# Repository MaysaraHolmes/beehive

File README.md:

# Real-Time Beehive Monitoring

We want to help beekeepers to keep an eye on their bees. By giving them insight on critical measurements we can monitor different events such as too low temperature, too high moisture, sufficient weight to harvest honey, as well as giving an estimate of how many bees went out of the beehive harvesting.

This project aims to set up a weather station with sensors and a fan to control the atmosphere inside the hive. The sensors output can be visualized through a website that can be hosted either locally on the Raspberry Pi, or hosted on the cloud (example [here](https://beehiveproject.herokuapp.com/)).
This project is done in partnership with the [Glasgow University Beekeeping Society](https://www.facebook.com/GUBeekeepingSociety/)

It was a success ! The Pi was able to make measurement of the ambiant temperature, pressure and humidity, as well as start the fan when the humidity got too high.

The website was displaying the value every 2 seconds while the fan was starting in as soon as the sensors triggered the alarm through a processor interrupt. Note, however, that the sensor provide data at more than 50Hz but it was decided the cap it to 2 second to avoid high traffic on the server (if hosted on the cloud).

## Table of contents
* [Setup](#setup)
* [General info](#general-info)
* [Technologies](#technologies)
* [Authors](#authors)
* [Images](#images)
* [Social media](#social-media)
## Setup

Instructions for installation can be found on the [installation wiki](https://github.com/MaysaraHolmes/beehive/wiki/Installation).

## General info
The code is simplified divided into three. Client, server and Fan. <br />
* The client is inteerupt by a timer every x millisecond reading the sensor data and sending it via udp to the server. <br />
* The server publish the data to our [example webpage](https://beehiveproject.herokuapp.com/) and saves the data to a database.
Additionally the server will send an email to registrered email-addresses everytime the humidity inside the beehive is too high. <br />
The website can be hosted either on a locally run server on the Raspberry Pi or hosted on a cloud based server.<br />
* The Fan is run depending on only one input pin. This pin is connected to the alarm on the humidity sensor inside the fan and will toggle instantaneously if the humidity goes above 80% humidity and off if it goes under 75% humidity. If the alarm pin toggles, it triggers an thread which will start or stop the fan depending if the pin goes high or low respectively. <br />
By this architecture the fan will be triggered even if the main code or the i2c bus fails to read the sensors. Making the code responsive and reliable. On the other hand if the alarm pin is disconnected you will still get an email/display on the webpage that the humidity inside the beehive is too high.
<br />
<br />
This projects architecture diagram:

Dependency graph for the C++ code:

The doxygen generated c++ documentation can be found here: [beehive_code_documentation](https://github.com/MaysaraHolmes/beehive/blob/master/documentation/beehive_code_documentation.pdf)

## Technologies

Project is created with:
* Raspberry pi 3.0
* Sensors
	* ADC101C021 ADC
	* HIH6131 Temperatur & Humidity x2
	* MPL115A2 Barometer
	* P82B96 I2C Shifter
* Node Js/express Js server
* MySQL database.
* [WiringPi](http://wiringpi.com/reference/core-functions/) 
* [CppTimer.h](https://github.com/berndporr/cppTimer) 

## Authors

* **Remy Chatel, 2411062**  - [Github](https://github.com/RemyChatel) (Main responsibility: Hardware)

* **Maysara Alhindi, 2417665**  - [Github](https://github.com/MaysaraHolmes) (Main responsibility: Nodejs Server side and Front-end)

* **Trine Ødegård Olsen, 2420036**  - [Github](https://github.com/trineoo) (Main responsibility: C++ code)

## Images

The beehives in the backyard in the university of Glasgow

Picture of the hardware, without the fan, soldered

## Social media
* [Hackster](https://www.hackster.io/maysara-alhindi/real-time-beehive-monitoring-glasgow-university-5a986c?fbclid=IwAR0-vXvfKS6yhzB5cdmx6wDfkbD9QhEtdo_F_e8NovsFujnpzO1nPfwy76o)
* [Hackaday](https://hackaday.io/project/164984-real-time-beehive-monitoring-glasgow-university)
* [Glasgow University Beekeeping Society](https://www.facebook.com/GUBeekeepingSociety/)

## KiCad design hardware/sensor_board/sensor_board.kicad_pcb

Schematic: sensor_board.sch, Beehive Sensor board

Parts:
C1: 0.1µ; C_0805_2012Metric_Pad1.15x1.40mm_HandSolder
C2: 0.22µ; C_0805_2012Metric_Pad1.15x1.40mm_HandSolder
C3, C4: 1µ; C_1206_3216Metric_Pad1.42x1.75mm_HandSolder
C5: 100n; C_0805_2012Metric_Pad1.15x1.40mm_HandSolder
J1: Conn_01x04; Molex_KK-254_AE-6410-04A_1x04_P2.54mm_Vertical
R1, R2, R3, R4, R5, R6: R; R_0805_2012Metric_Pad1.15x1.40mm_HandSolder
U1: HIHxx3x-021; SOIC-8_3.9x4.9mm_P1.27mm
U2: P82B96; SOIC-8_3.9x4.9mm_P1.27mm
U3: MPL115A2; LGA-8_3x5mm_P1.25mm

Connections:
+3V3: C2.1, C4.1, C5.1, J1.1, R1.1, R2.1, R3.1, R4.1, R5.2, R6.2, U1.8 (VDD), U2.8 (VCC), U3.1 (VDD)
/SCL: R2.2, U1.3 (SCL), U2.7 (SCL), U3.8 (SCL)
/SCL_ext: J1.2, R4.2, U2.2 (RXD-SDA), U2.3 (TXD-SDA)
/SDA: R1.2, U1.4 (SDA), U2.1 (SDA), U3.7 (SDA)
/SDA_ext: J1.3, R3.2, U2.5 (TXD-SCL), U2.6 (RXD-SCL)
/Vcore: C1.1, U1.1 (Vcore)
/alarm: U1.5 (AL_H)
GND: C1.2, C2.2, C3.2, C4.2, C5.2, J1.4, U1.2 (VSS), U2.4 (GND), U3.3 (GND)
unnamed: C3.1, U3.2 (CAP)
unnamed: R5.1, U3.5 (~RST)
unnamed: R6.1, U3.4 (~SHDN)

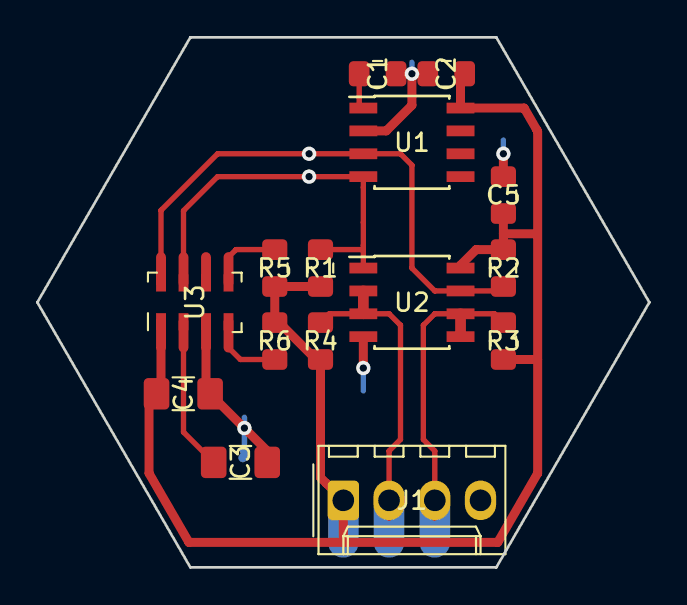
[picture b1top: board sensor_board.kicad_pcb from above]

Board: 2 copper layers, 34.0 x 29.4 mm, 15 parts (0 on the bottom side), 10 nets.

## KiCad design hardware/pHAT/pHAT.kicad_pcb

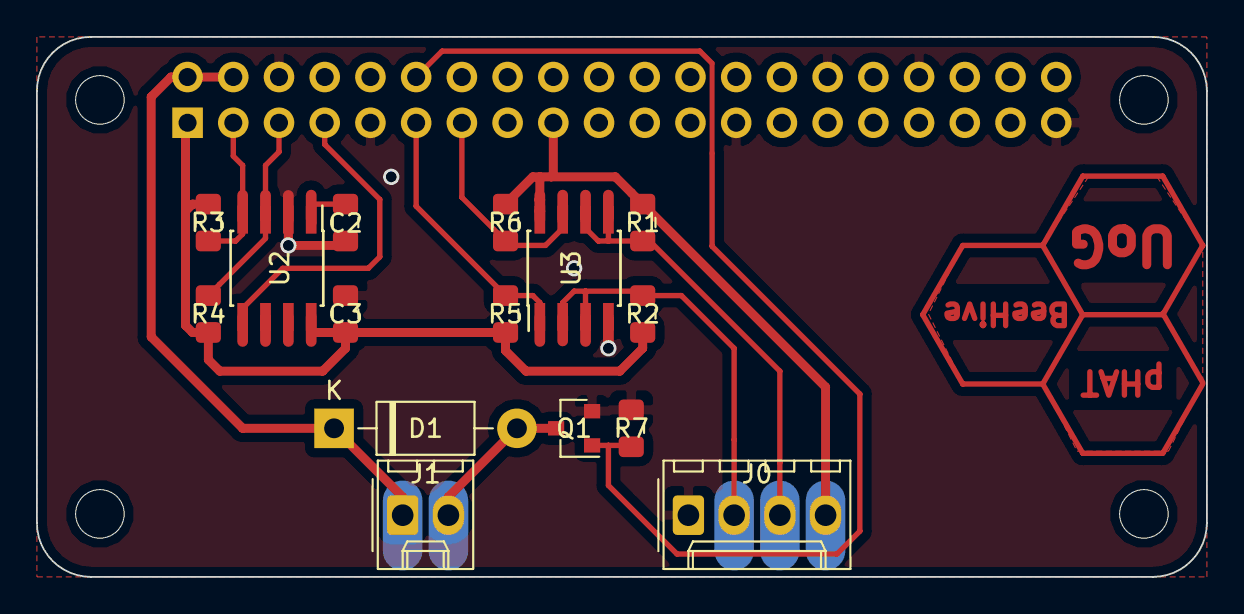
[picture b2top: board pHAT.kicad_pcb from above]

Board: 2 copper layers, 65.0 x 30.0 mm, 20 parts (1 on the bottom side), 13 nets.

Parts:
C2: 0.1µ; C_0805_2012Metric_Pad1.15x1.40mm_HandSolder
C3: 0.22µ; C_0805_2012Metric_Pad1.15x1.40mm_HandSolder
D1: 1N4007; D_DO-41_SOD81_P10.16mm_Horizontal
J0: Conn_01x04; Molex_KK-254_AE-6410-04A_1x04_P2.54mm_Vertical
J1: Conn_01x02; Molex_KK-254_AE-6410-02A_1x02_P2.54mm_Vertical
MK1, MK2, MK3, MK4: M2.5; MountingHole_2.7mm_M2.5
P1: Conn_02x20_Odd_Even; PinSocket_2x20_P2.54mm_Vertical
Q1: 2N7002; SOT-23
R1, R2, R3, R4, R5, R6, R7: 5K; R_0805_2012Metric_Pad1.15x1.40mm_HandSolder
U2: HIH6131-021; SOIC-8_3.9x4.9mm_P1.27mm
U3: P82B96; SOIC-8_3.9x4.9mm_P1.27mm

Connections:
+3V3: C3.1, J0.4, P1.1, P1.17, R1.1, R2.1, R3.1, R4.1, R5.1, R6.1, U2.8, U3.8
+5V: D1.1, J1.1, P1.2, P1.4
/SCL0: P1.5, R4.2, U2.3
/SCL1: P1.13, R6.2, U3.7
/SCLA: J0.3, R1.2, U3.5, U3.6
/SDA0: P1.3, R3.2, U2.4
/SDA1: P1.11, R5.2, U3.1
/SDAA: J0.2, R2.2, U3.2, U3.3
/Vcore: C2.1, U2.1
/alarm_hive: P1.7, U2.5
/cmd: P1.12, Q1.1, R7.1
/fan_cmd: D1.2, J1.2, Q1.3
GND: C2.2, C3.2, J0.1, P1.6, P1.9, P1.14, P1.20, P1.25, P1.30, P1.34, P1.39, Q1.2, R7.2, U2.2, U3.4

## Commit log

2019-01-18 init server
2019-01-18 datasheet upload
    Uploading datasheets of the various components (ADC, I2C multiplexer, and sensors)
2019-01-20 basic front-end desing
2019-01-21 pHAT base board
    Creation of the pHAT board
2019-01-21 First version of PCB for pHAT
2019-01-22 graphical improvements to PCB
    Added a logo and cleaned some tracks
2019-01-22 First version of sensor board
    Added a sensor board for the HIH61 humidity and temperature sensor
2019-01-22 add system folder with some basic files to test
2019-01-23 small changes to test on the raspberry
2019-01-23 Testing I2C on RPI
2019-01-23 add charts
2019-01-23 Adding documentation
2019-01-23 Moving form multiplexer to two I2C busses
    Changed from using one I2C bus with a multiplexer to using two I2C busses with the addition of level shifters
2019-01-26 Sensor board v2 and improvements to pHAT
    Added a I2C level shifter to the sensor board, which lead to a complete redesign
    Some graphical improvements to the pHAT
2019-01-28 adding pic
2019-01-28 Added ArchitectureDiagram.xml for presentation
2019-01-28 Added architecture diagram image
2019-01-28 Updated Architecture Diagram
2019-01-29 Added the alarm pin for humidity
    Added support for the alarm pin of the HIH6131 in order to detect through interrupt a high level of humidity
2019-01-30 add makefile
2019-01-30 Adding smd pad for connectors
    Adding SMD pads to allow surface soldering at right angle of Molex JYK connectors
2019-01-30 add makefile to src/system
2019-01-30 changed the makefile, use make run
2019-01-30 added smalle changes to read the i2c buffer
2019-01-30 testing bitset
2019-01-30 bitset workinggit status
2019-01-31 add the temp and hum module, but need to check MSB and LSB
2019-01-31 add the humidity equation
2019-02-02 add small changes to the I2C and TemperaturAndHumidity
2019-02-02 change the I2C template, add template ADC
2019-02-06 testing temp&hum
2019-02-06 print sentence
2019-02-06 make global_buffer
2019-02-06 add print sentence
2019-02-06 add print
2019-02-06 print
2019-02-06 changed the global buffer
2019-02-06 add main functions
2019-02-06 test reading from sensor
2019-02-06 changing pointer
2019-02-06 hanging the printing in I2c
2019-02-06 its working
2019-02-06 calculating the temp
2019-02-06 added integer I2c
2019-02-06 print bits
2019-02-06 testing temp
2019-02-06 testing temp2
2019-02-06 going home
2019-02-11 add change, setting global_buffer to unsigned int
2019-02-11 add usnigned int
2019-02-11 add bitshifting
2019-02-11 printing out bit
2019-02-11 add the temp and hum equation
2019-02-11 printing the bitsets again
2019-02-11 double checking the humidity bits
2019-02-11 Can not do math in c...
2019-02-11 comment in function..
2019-02-11 change to use the pow function
2019-02-11 cleaning the code
2019-02-11 cleaning comments
2019-02-11 Add new class for thread: reading all devices
2019-02-12 Start of hardware redesign
2019-02-12 Sensor Board v3.0
    Removed ADC converter, moved the hive temp&hum sensor to the main board that will now be placed inside the hive
2019-02-13 adding database
2019-02-13 temp data
2019-02-17 testing class ReadAllDevices
2019-02-17 Preparing layout for adding a fan
2019-02-18 test if i2c-3 is open
2019-02-18 add thread to read sensors
2019-02-18 Finished fan command circuit (pHAT v3.2)
2019-02-18 add abstract sensor class
2019-02-18 add abstract sensor class, actually including the sensor.hpp file
2019-02-20 add CppTimer, not implement
2019-02-20 sockets not completed
2019-02-20 Add first draft Pressure-class
2019-02-27 sockets working
2019-02-27 add testing code for the fan/gpio pin
2019-02-27 rendering data
2019-02-27 Pwm working on pin1, gpio18
2019-02-27 add reading both the temp/hum-sensors
2019-02-27 change one parameter-name
2019-03-01 clean comments, remove code for SPI
2019-03-01 Add one comment, succeeded reading I2C-bus
2019-03-01 testing softPwm pin 13
2019-03-04 add CppTimer
2019-03-06 wiringpi-lib working with the fan
2019-03-06 adding env vars and DB host setup
2019-03-06 fixing bugs
2019-03-11 Remove makefile and add cmake instead + add CppTimer class and test in main
2019-03-12 add class Fan
2019-03-12 add testing code fan
2019-03-12 Rework of sensor board and correction of pHAT
2019-03-12 Fan and timer is working on RaspberryPi
2019-03-12 updated gitignore
2019-03-12 Timer starts thread to read sensors, working
2019-03-12 add class Pressure Sensor
2019-03-12 add include pressure in ReadAllDevices
2019-03-13 add boost/asio udp code
2019-03-13 add differen UDP lib
2019-03-13 add I2C addr for pressure sensor
2019-03-13 add code for reading all the sensors
2019-03-13 fix bug writing sensors
2019-03-13 fixing caps look code..
2019-03-13 fixing caps look code2..
2019-03-13 reading and printing the temp bits
2019-03-13 printing the actual bits
2019-03-13 cast to unsigned int
2019-03-14 fix bug ReadI2CDevices in constructor
2019-03-15 CHanging the formula Pressure sensor
2019-03-15 adding pressure comp
2019-03-18 adding udp connection and fixing clinet sockets
2019-03-18 realtime updating
2019-03-19 add testing code for UDP
2019-03-19 add UDP code to class
2019-03-19 add pressure coefficients in pressure class
2019-03-19 comment the code so we can figure out why the coefficients reads zero
2019-03-20 test hyjnu
2019-03-20 Polishing the board
2019-03-20 add includes
2019-03-20 client working
2019-03-20 sending correct data to server
2019-03-20 the client is done, sending the correct data, yeah
2019-03-23 add function to receive interrupts on spesifiec pin
2019-03-23 add pressure coefficients, trying to read
2019-03-24 Modified ArchitectureDiagram.png
2019-03-24 Added link to installation wiki
2019-03-24 Fixed position error for a link
2019-03-24 Renaming and cleaning documentation folder
2019-03-24 Adding the manufacturing files
2019-03-25 comment outdouble declaration of fan in main
2019-03-25 makie static helper function for thread
2019-03-25 correct interrupt code
2019-03-25 testing more general interrupt code in Fan
2019-03-25 try making it work
2019-03-25 add evverything to hpp file
2019-03-25 email_sending_fix
2019-03-25 remove print sentences and send pressure data to server
2019-03-25 adding pressure
2019-03-25 Cleaning up some directories
2019-03-25 add system_setup fro programming the humid sensor
2019-03-25 Adding boards datasheets
2019-03-25 write correct bit....
2019-03-25 fix styles
2019-03-25 start script
2019-03-25 Correction to README and added documentation
2019-03-25 set humidity alarm
2019-03-25 add print sentence alarm pin
2019-03-25 add eroor msgs
2019-03-25 writing correct to temp&hum sensor- alarm should be configured correct
2019-03-25 stupid wiringPi library doesnt work
2019-03-26 add print-sentence to debug
2019-03-26 add static pointer to the fan
2019-03-26 clean the code, ready to use, if digitalRead is working
2019-03-26 done everything in software to make wiringPi work. Only read high on gpio 7
2019-03-26 testing hard-coding fan
2019-03-26 fix segmentation fault...
2019-03-26 fan is workinggit status git status eveerything is working - HAPPY TRINE
2019-03-27 email sending
2019-03-27 port and title
2019-03-29 refining code
2019-04-01 removing a lot of comments and deleting test functions
2019-04-13 doxygen comments I2C
2019-04-13 doxygen comments Temperatur&humidity
2019-04-13 doxygen comments Pressure
2019-04-13 doxygen comments Sensor
2019-04-13 doxygen comments ReadI2CDevices
2019-04-13 doxygen comments Fan
2019-04-13 doxygen comments TimerEvent, delete Cpptimer.cpp and made a new class instead
2019-04-13 doxygen comments in main
2019-04-13 rename main to beehive and change cmake
2019-04-13 Update readme image-paths
2019-04-13 remove includes, add dependency graph
2019-04-13 add doxyfile
2019-04-13 remove and add the doxyfile
2019-04-14 add doxygen pdf to documentation
2019-04-14 removed wiringpi lib in the cmakefile in the setup
2019-04-14 add pictures
2019-04-14 adding commets and refactoring the code
2019-04-14 refine code
2019-04-14 More detailed explaination
2019-04-14 Clarifying an information and correcting typo
2019-04-14 Adding pictures
2019-04-14 social media links
